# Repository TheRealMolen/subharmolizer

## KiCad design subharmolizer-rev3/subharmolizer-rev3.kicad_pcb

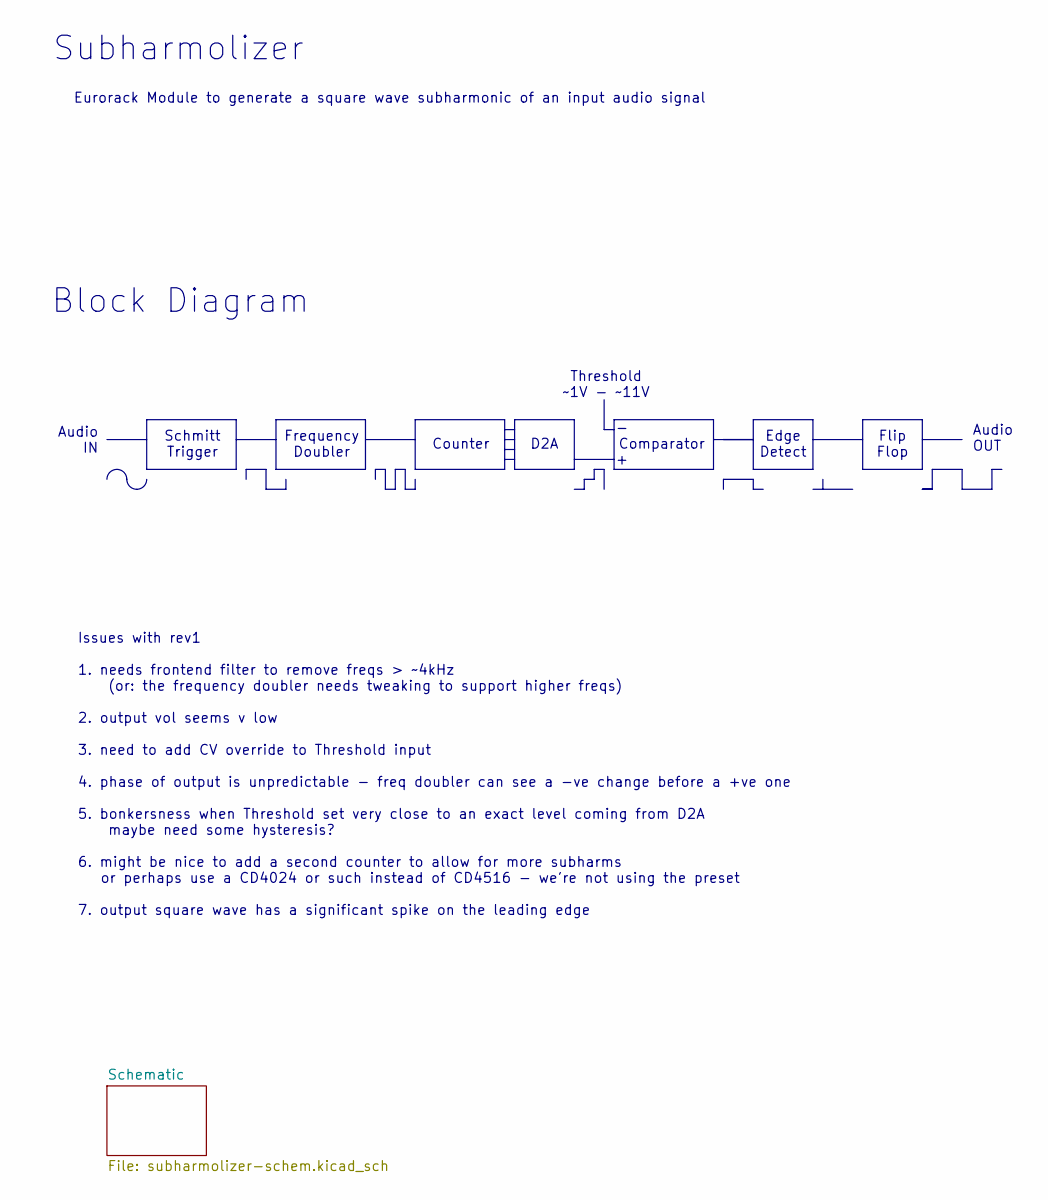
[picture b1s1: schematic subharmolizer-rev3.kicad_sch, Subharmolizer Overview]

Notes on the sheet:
Schmitt Trigger
Edge Detect
Block Diagram
Flip Flop
Threshold ~1V - ~11V
Subharmolizer
Audio IN
Issues with rev1 1. needs frontend filter to remove freqs > ~4kHz (or: the frequency doubler needs tweaking to support higher freqs) 2. output vol seems v low 3. need to add CV override to Threshold input 4. phase of output is unpredictable - freq doubler can see a -ve change before a +ve one 5. bo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
D2A
Comparator
Frequency Doubler
Counter
Eurorack Module to generate a square wave subharmonic of an input audio signal
Audio OUT

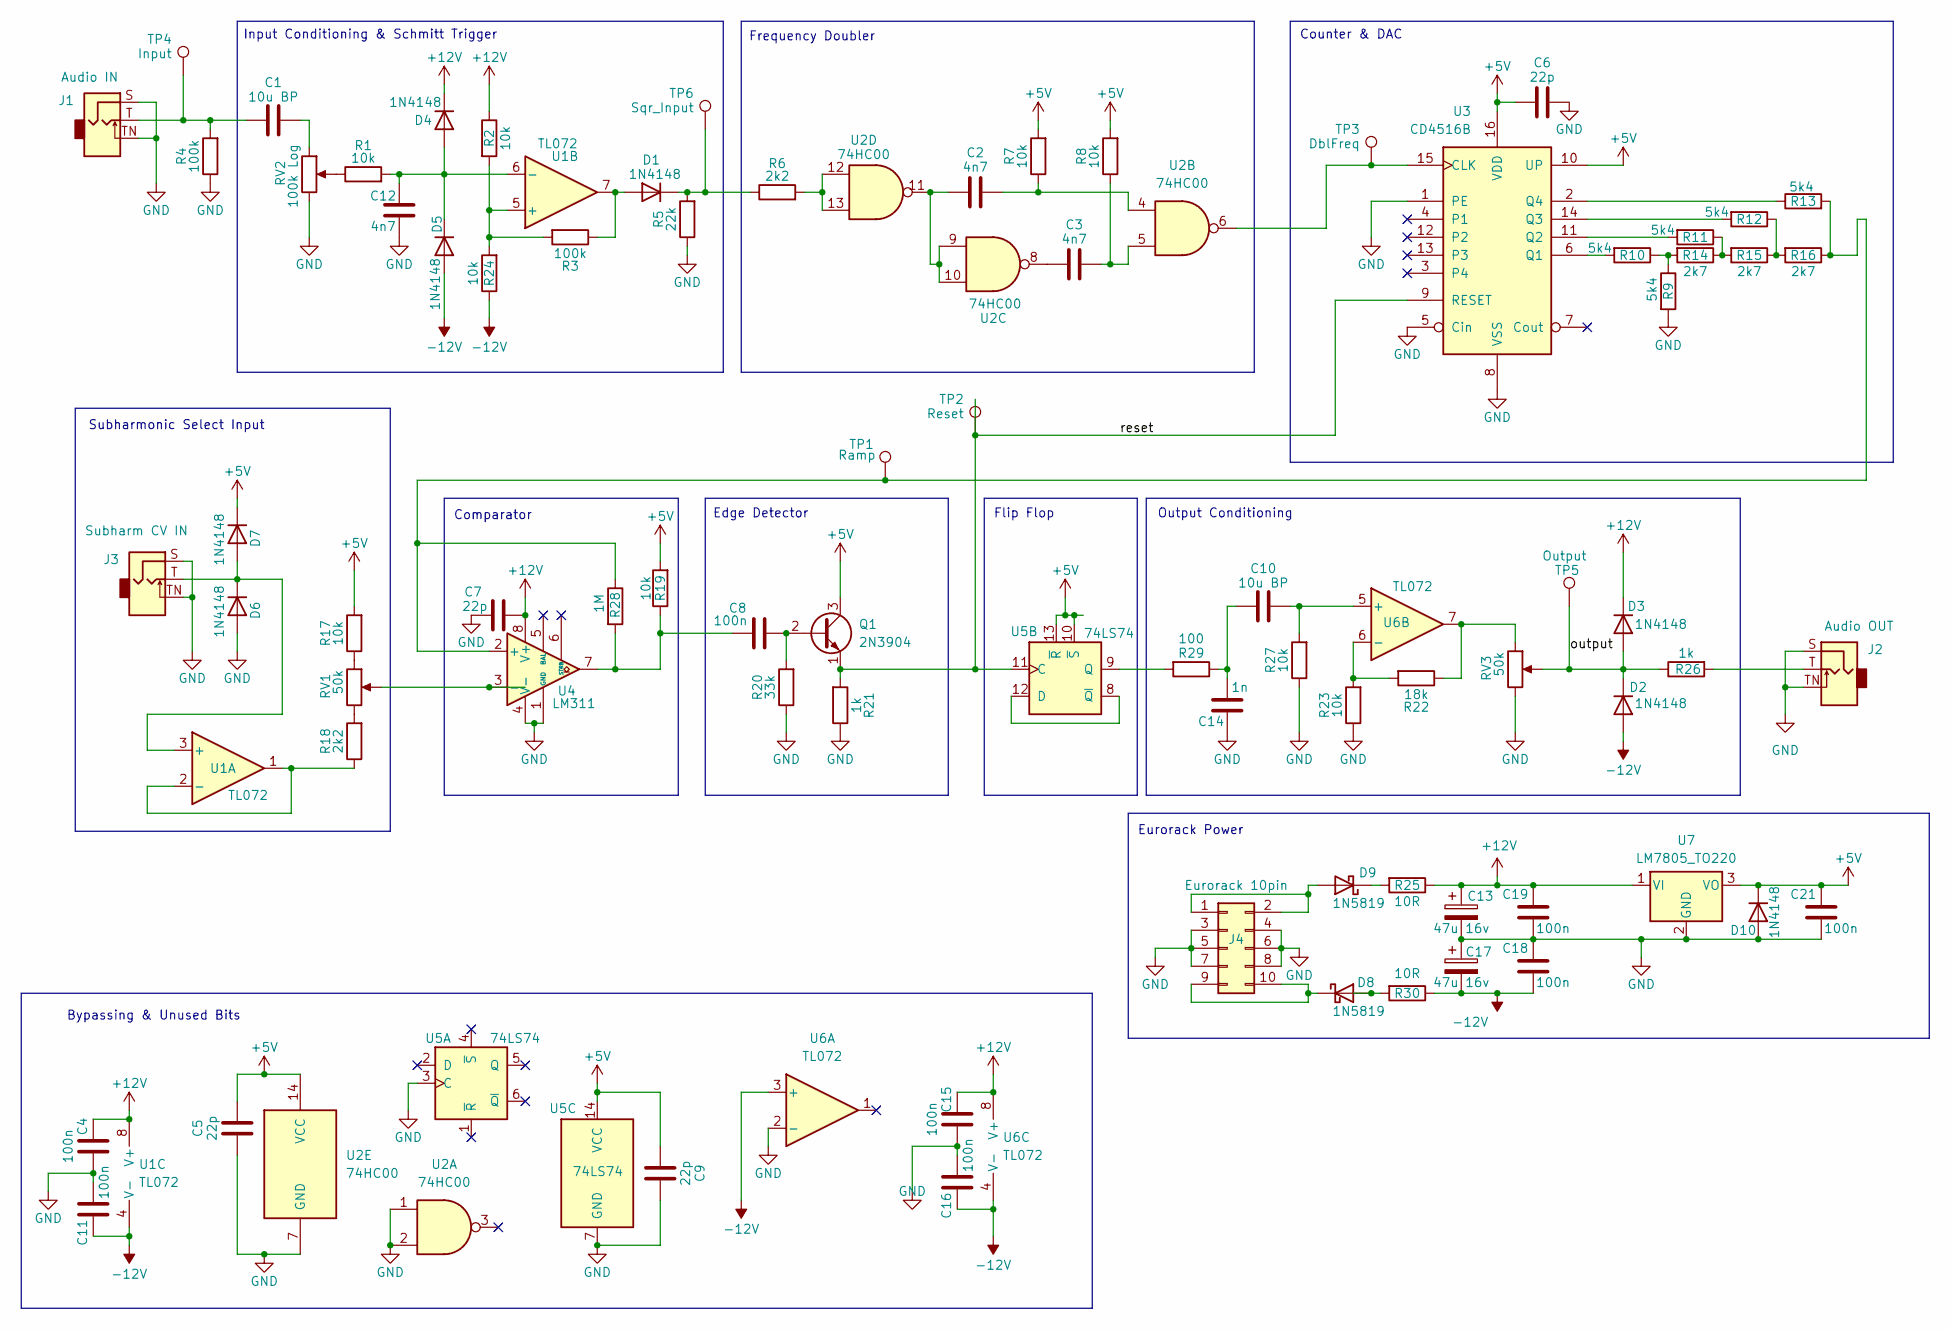
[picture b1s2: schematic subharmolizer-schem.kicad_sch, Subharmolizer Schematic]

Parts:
C1, C10: 10u BP; C_Radial_D5.0mm_H5.0mm_P2.00mm
C2, C3, C12: 4n7; C_Rect_L7.0mm_W2.5mm_P5.00mm
C4, C8, C11, C15, C16, C18, C19, C21: 100n; C_Rect_L7.0mm_W2.5mm_P5.00mm
C5, C6, C7, C9: 22p; C_Disc_D3.8mm_W2.6mm_P2.50mm
C13, C17: 47u 16v; CP_Radial_D5.0mm_P2.00mm
C14: 1n; C_Rect_L7.0mm_W2.5mm_P5.00mm
D1, D2, D3, D4, D5, D6, D7, D10: 1N4148; D_DO-35_SOD27_P7.62mm_Horizontal
D8, D9: 1N5819; D_DO-41_SOD81_P10.16mm_Horizontal
J1: Audio IN; Jack_3.5mm_QingPu_WQP-PJ398SM_Vertical
J2: Audio OUT; Jack_3.5mm_QingPu_WQP-PJ398SM_Vertical
J3: Subharm CV IN; Jack_3.5mm_QingPu_WQP-PJ398SM_Vertical
J4: Eurorack 10pin; IDC-Header_2x05_P2.54mm_Vertical
Q1: 2N3904; TO-92_Inline
R1, R2, R7, R8, R17, R19, R23, R24, R27: 10k; R_Axial_DIN0207_L6.3mm_D2.5mm_P7.62mm_Horizontal
R3, R4: 100k; R_Axial_DIN0207_L6.3mm_D2.5mm_P7.62mm_Horizontal
R5: 22k; R_Axial_DIN0207_L6.3mm_D2.5mm_P7.62mm_Horizontal
R6, R18: 2k2; R_Axial_DIN0207_L6.3mm_D2.5mm_P7.62mm_Horizontal
R9, R10, R11, R12, R13: 5k4; R_Axial_DIN0207_L6.3mm_D2.5mm_P2.54mm_Vertical
R14, R15, R16: 2k7; R_Axial_DIN0207_L6.3mm_D2.5mm_P2.54mm_Vertical
R20: 33k; R_Axial_DIN0207_L6.3mm_D2.5mm_P7.62mm_Horizontal
R21, R26: 1k; R_Axial_DIN0207_L6.3mm_D2.5mm_P7.62mm_Horizontal
R22: 18k; R_Axial_DIN0207_L6.3mm_D2.5mm_P7.62mm_Horizontal
R25, R30: 10R; R_Axial_DIN0207_L6.3mm_D2.5mm_P7.62mm_Horizontal
R28: 1M; R_Axial_DIN0207_L6.3mm_D2.5mm_P7.62mm_Horizontal
R29: 100; R_Axial_DIN0207_L6.3mm_D2.5mm_P7.62mm_Horizontal
RV1, RV3: 50k; Potentiometer_Alpha_RD901F-40-00D_Single_Vertical_CircularH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
RV2: 100k Log; Potentiometer_Alpha_RD901F-40-00D_Single_Vertical_CircularH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
TP1: Ramp; TestPoint_THTPad_D1.0mm_Drill0.5mm
TP2: Reset; TestPoint_THTPad_D1.0mm_Drill0.5mm
TP3: DblFreq; TestPoint_THTPad_D1.0mm_Drill0.5mm
TP4: Input; TestPoint_THTPad_D1.0mm_Drill0.5mm
TP5: Output; TestPoint_THTPad_D1.0mm_Drill0.5mm
TP6: Sqr_Input; TestPoint_THTPad_D1.0mm_Drill0.5mm
U1, U6: TL072; DIP-8_W7.62mm
U2: 74HC00; DIP-14_W7.62mm
U3: CD4516B; DIP-16_W7.62mm
U4: LM311; DIP-8_W7.62mm
U5: 74LS74; DIP-14_W7.62mm
U7: LM7805_TO220; TO-220-3_Vertical

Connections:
+5V: C5.2, C6.1, C9.1, C21.2, D7.1 (K), D10.1 (K), Q1.3 (C), R7.2, R8.2, R17.2, R19.2, U2.14 (VCC), U3.10 (UP), U3.16 (VDD), U5.10 (~S), U5.13 (~R), U5.14 (VCC), U7.3 (VO)
+12V: C4.2, C7.1, C13.1, C15.2, C19.2, D3.1 (K), D4.1 (K), R2.1, R25.1, U1.8 (V+), U4.8 (V+), U6.8 (V+), U7.1 (VI)
-12V: C11.1, C16.1, C17.2, C18.1, D2.2 (A), D5.2 (A), R24.1, R30.1, U1.4 (V-), U6.3 (+), U6.4 (V-)
/Schematic/output: D2.1 (K), D3.2 (A), R26.1, RV3.2, TP5.1
/Schematic/reset: Q1.1 (E), R21.2, TP2.1, U3.9 (RESET), U5.11 (C)
GND: C4.1, C5.1, C6.2, C7.2, C9.2, C11.2, C12.1, C13.2, C14.1, C15.1, C16.2, C17.1, C18.2, C19.1, C21.1, D6.2 (A), D10.2 (A), J1.S, J1.TN, J2.S, J2.TN, J3.S, J3.TN, J4.3, J4.4, J4.5, J4.6, J4.7, J4.8, R4.1, R5.1, R9.2, R20.1, R21.1, R23.1, R27.1, RV2.3, RV3.3, U2.1, U2.2, U2.7 (GND), U3.1 (PE), U3.5 (Cin), U3.8 (VSS), U4.1 (GND), U4.4 (V-), U5.3 (C), U5.7 (GND), U6.2 (-), U7.2 (GND)
unnamed: C1.1, J1.T, R4.2, TP4.1
unnamed: C1.2, RV2.1
unnamed: C2.1, U2.9, U2.10, U2.11
unnamed: C2.2, R7.1, U2.4
unnamed: C3.1, U2.8
unnamed: C3.2, R8.1, U2.5
unnamed: C8.2, R19.1, R28.2, U4.7
unnamed: C10.1, C14.2, R29.1
unnamed: D1.2 (A), R3.1, U1.7
unnamed: D1.1 (K), R5.2, R6.1, TP6.1
unnamed: C12.2, D4.2 (A), D5.1 (K), R1.2, U1.6 (-)
unnamed: D6.1 (K), D7.2 (A), J3.T, U1.3 (+)
unnamed: D8.2 (A), R30.2
unnamed: D8.1 (K), J4.9, J4.10
unnamed: D9.2 (A), J4.1, J4.2
unnamed: D9.1 (K), R25.2
unnamed: J2.T, R26.2
unnamed: C8.1, Q1.2 (B), R20.2
unnamed: R1.1, RV2.2
unnamed: R6.2, U2.12, U2.13
unnamed: R9.1, R10.1, R14.2
unnamed: R11.1, R14.1, R15.2
unnamed: R12.1, R15.1, R16.2
unnamed: R17.1, RV1.1
unnamed: R18.2, RV1.3
unnamed: R22.1, RV3.1, U6.7
unnamed: R18.1, U1.1, U1.2 (-)
unnamed: R2.2, R3.2, R24.2, U1.5 (+)
unnamed: TP3.1, U2.6, U3.15 (CLK)
unnamed: R10.2, U3.6 (Q1)
unnamed: R11.2, U3.11 (Q2)
unnamed: R12.2, U3.14 (Q3)
unnamed: R13.1, U3.2 (Q4)
unnamed: R13.2, R16.1, R28.1, TP1.1, U4.2 (+)
unnamed: RV1.2, U4.3 (-)
unnamed: U5.8 (~Q), U5.12 (D)
unnamed: R29.2, U5.9 (Q)
unnamed: C10.2, R27.2, U6.5 (+)
unnamed: R22.2, R23.2, U6.6 (-)

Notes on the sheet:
Bypassing & Unused Bits
Eurorack Power
Frequency Doubler
Counter & DAC
Edge Detector
Input Conditioning & Schmitt Trigger
Flip Flop
Output Conditioning
Comparator
Subharmonic Select Input

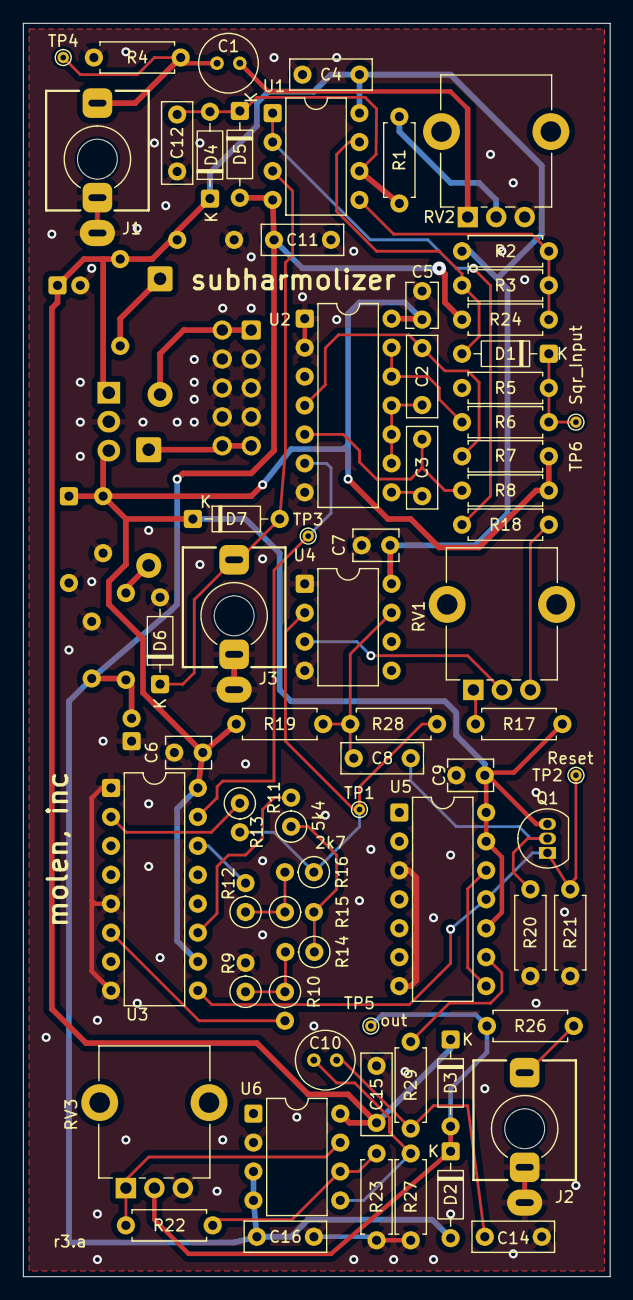
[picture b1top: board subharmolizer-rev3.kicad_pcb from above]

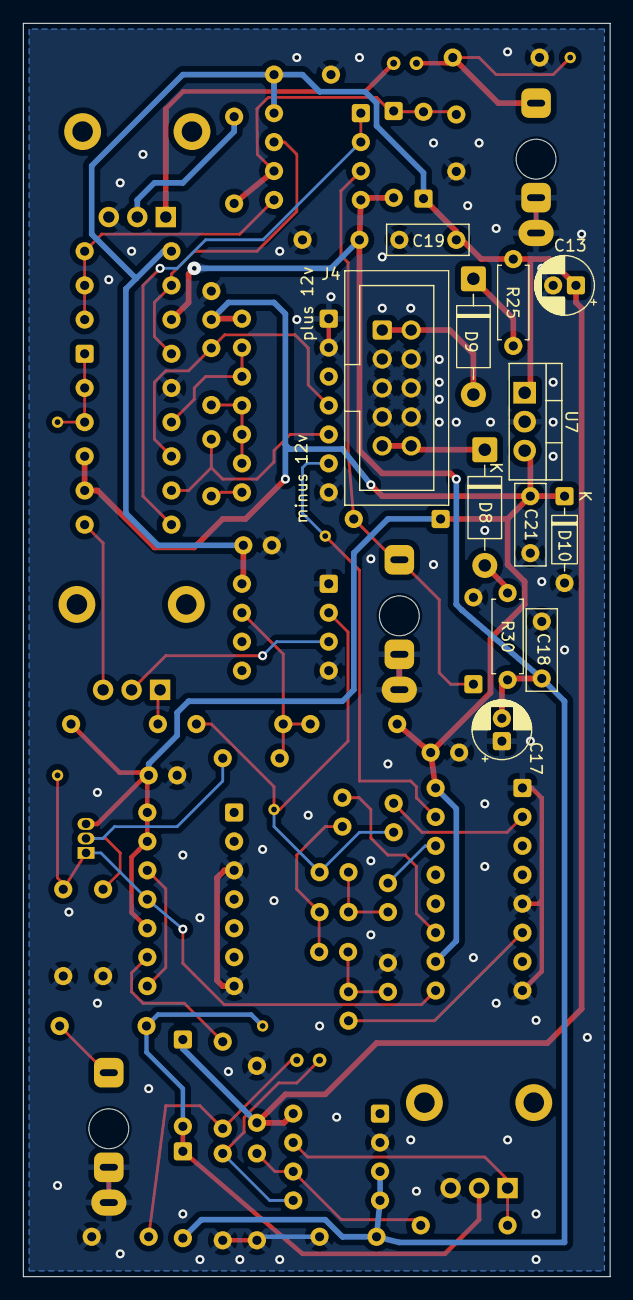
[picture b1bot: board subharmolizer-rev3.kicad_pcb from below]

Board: 2 copper layers, 51.5 x 110.0 mm, 81 parts (12 on the bottom side), 45 nets.

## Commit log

2025-09-20 rev2 tweaks
2025-10-19 rev3 & work towards pcb
2025-10-19 rev3.a pcb fully routed and ready for fab
